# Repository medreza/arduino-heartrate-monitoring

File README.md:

# arduino-heartrate-monitoring

Heartrate monitoring based on photodiode sensor and Arduino. Uses Processing for user interface.

This was mini project for Electronics Instrumentation 2014 class in FMIPA Universitas Gadjah Mada. 

The video of this project can be seen on:
https://www.youtube.com/watch?v=Lp79tmzNe8U

### Some pics

### Credit goes to team members
- Aditya Riska Putra
- Ahmed Reza Rafsanzani
- Ryan Eko Saputro
- Zainul Anam

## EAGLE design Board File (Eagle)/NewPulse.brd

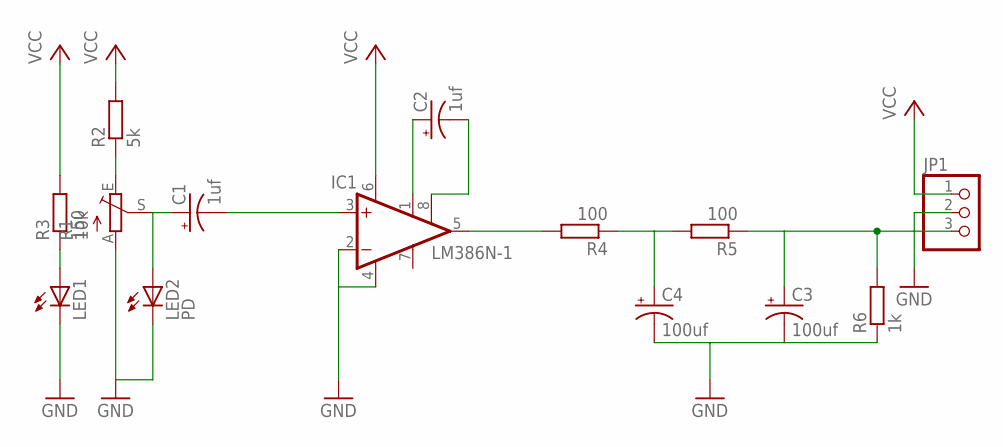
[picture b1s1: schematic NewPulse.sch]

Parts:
C1, C2: 1uf; E2-5
C3, C4: 100uf; E2-5
IC1: LM386N-1; DIL08
JP1: PINHD-1X3/90; 1X03/90
LED1: LED5MM
LED2: PD; LED5MM
R1: 10k; CA6V
R2: 5k; 0207/10
R3: 150; 0207/10
R4, R5: 100; 0207/10
R6: 1k; 0207/10

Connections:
GND: C3.-, C4.-, IC1.2 (-IN), IC1.4 (GND), JP1.2, LED1.K (C), LED2.K (C), R1.A, R6.1
unnamed: LED1.A, R3.1
unnamed: R1.E, R2.1
unnamed: C1.+, LED2.A, R1.S
unnamed: C1.-, IC1.3 (+IN)
unnamed: C2.+, IC1.1 (GAIN)
unnamed: C2.-, IC1.8 (GAIN)
unnamed: IC1.5 (OUT), R4.2
unnamed: C4.+, R4.1, R5.2
unnamed: C3.+, JP1.3, R5.1, R6.2
VCC: IC1.6 (VS), JP1.1, R2.2, R3.2

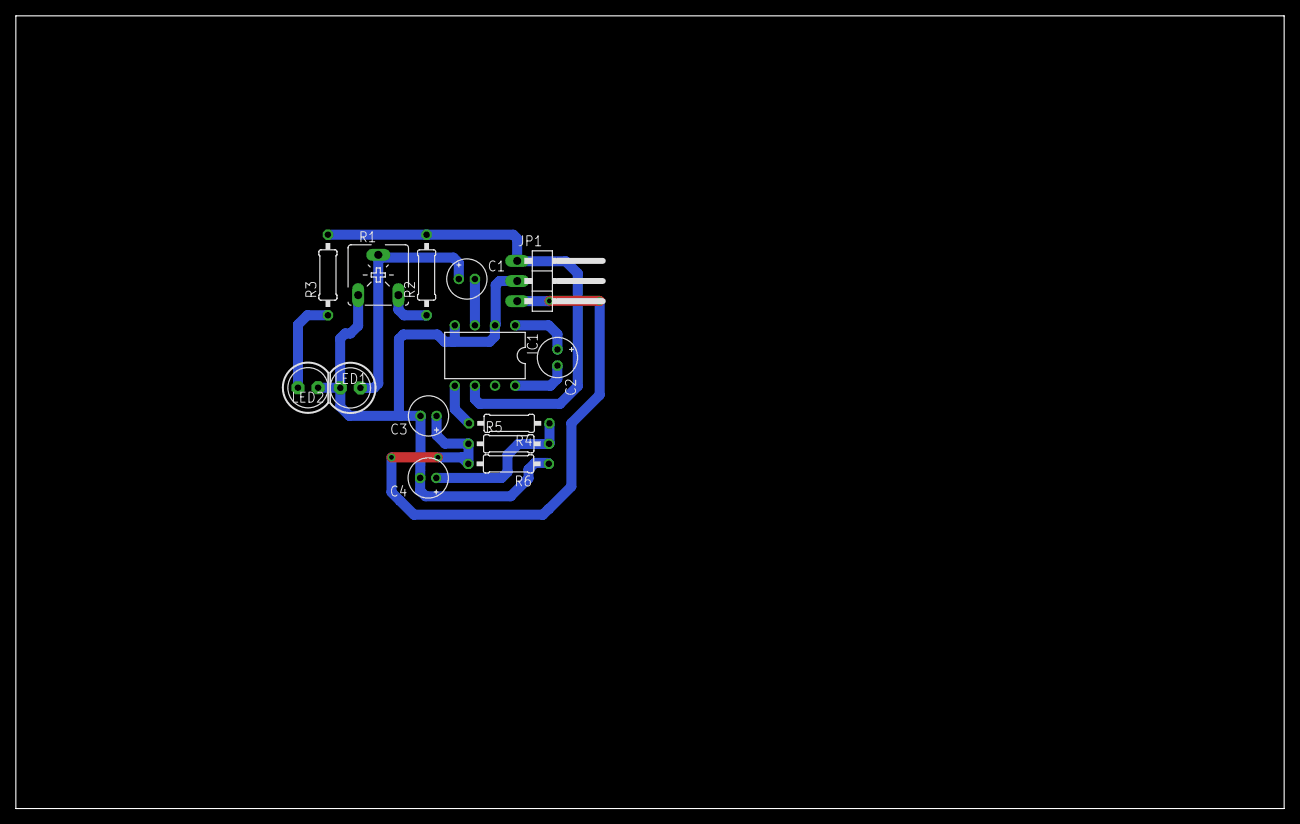
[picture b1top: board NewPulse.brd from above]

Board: 2 copper layers, 160.0 x 100.0 mm, 14 parts (0 on the bottom side), 11 nets.

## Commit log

2018-08-19 found the newest program (i think)
2018-08-19 add pics
